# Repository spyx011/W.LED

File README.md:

# W LED Keychain

A keychain PCB with 13 blue LEDs in the shape of a W. It runs on a small LiPo battery and charges over USB-C.

## What's on it

- 13 blue 5mm LEDs in a W (front side)
- ATtiny1616 chip
- 2x 74HC595 and 2x ULN2003A to drive the LEDs
- LiPo battery on a JST connector, charged by USB-C
- Boost converter for 5V
- Slide switch and a push button
- My logo on the back

## Board

- 4 layers, 1.6mm, black solder mask
- Made in KiCad 10
- LEDs on the front, everything else on the back

- 

##3D model

## How the LEDs work

The ATtiny sends data to the two 74HC595 chips. They feed the ULN2003A chips, and those turn the LEDs on and off.

| ATtiny pin | Goes to |
|---|---|
| PA0 | UPDI header |
| PA1 | 595 data in |
| PA3 | 595 shift clock |
| PA4 | 595 latch |
| PB0 | 595 output enable (brightness) |
| PA6 | Push button |

## Programming

Turn the switch off, take the battery out, and connect a UPDI programmer to the 3 pin header (UPDI, 5V, GND).

## Files

- `hardware` - KiCad files
- `manufacturing` - Gerbers and BOM
- `docs` - pictures

Open `w.led.kicad_pro` in KiCad to see the design.

## Ordering

Pick 4 layers, 1.6mm, black solder mask. Use a LiPo with a protection board, because the charger chip doesn't protect the battery.

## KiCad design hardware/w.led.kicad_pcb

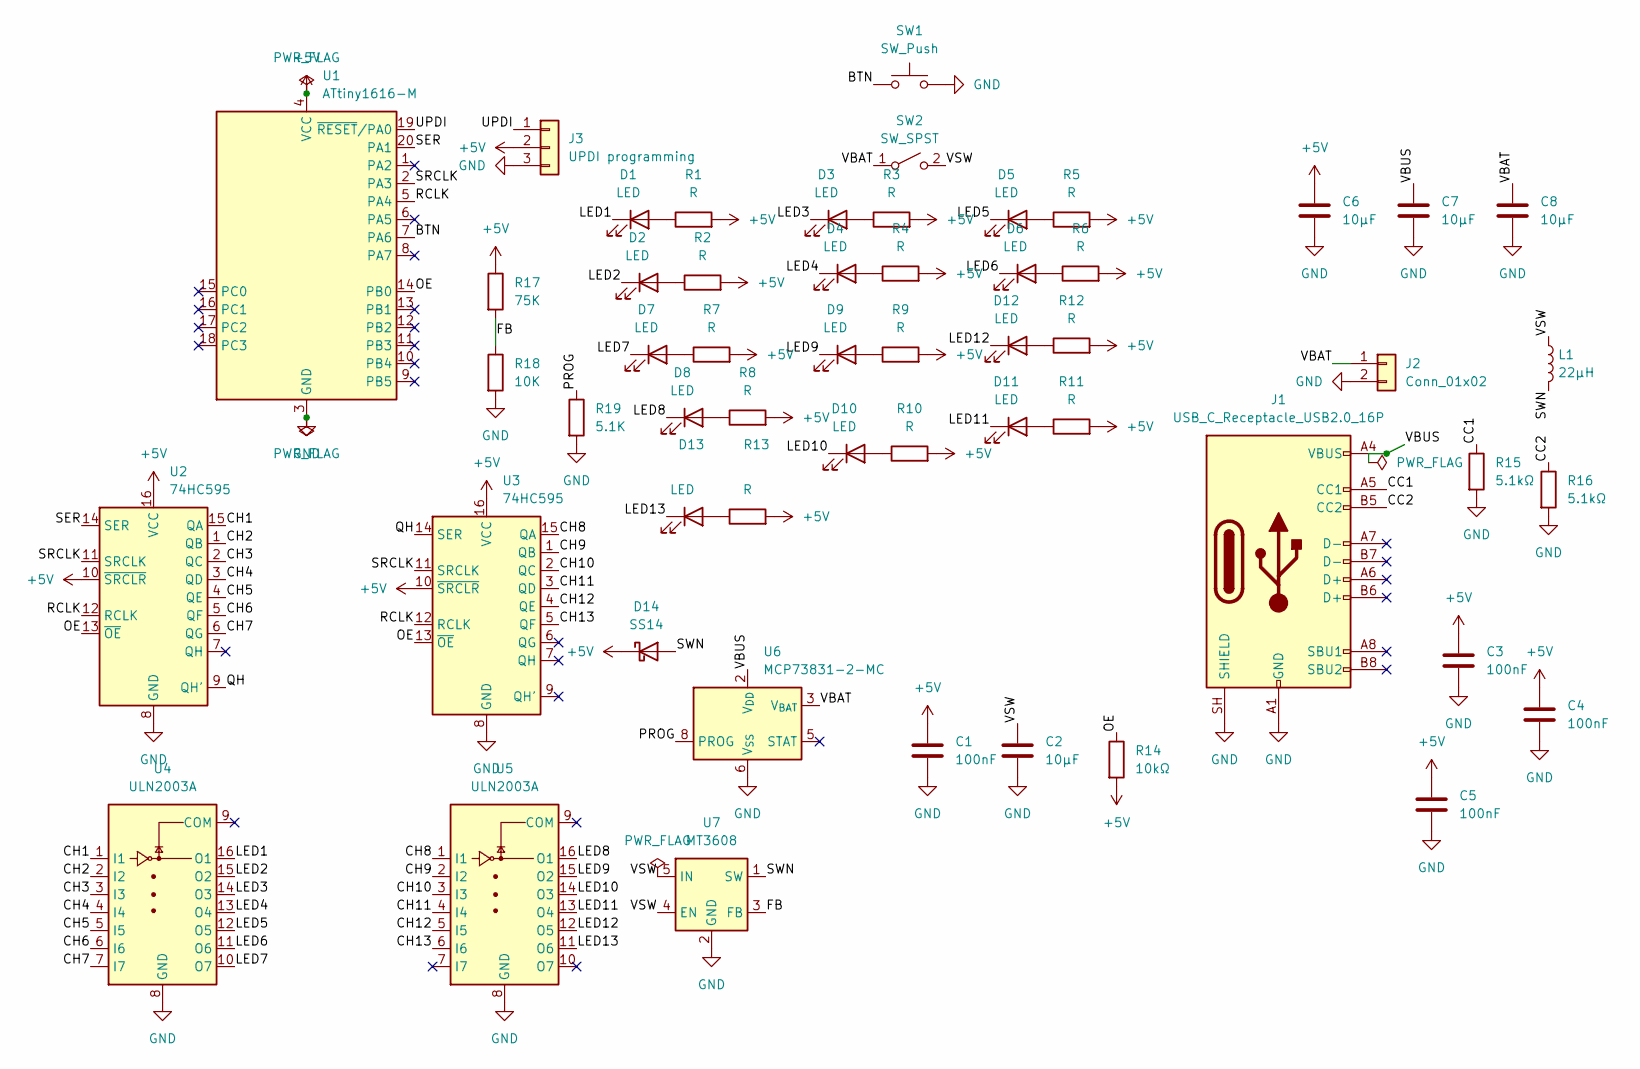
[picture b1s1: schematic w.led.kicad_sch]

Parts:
C1, C3, C4, C5: 100nF; C_0603_1608Metric
C2, C6, C7, C8: 10µF; C_0805_2012Metric
D1, D2, D3, D4, D5, D6, D7, D8, D9, D10, D11, D12, D13: LED; LED_D5.0mm
D14: SS14; D_SMA
J1: USB_C_Receptacle_USB2.0_16P; USB_C_Receptacle_GCT_USB4105-xx-A_16P_TopMnt_Horizontal
J2: Conn_01x02; JST_PH_B2B-PH-K_1x02_P2.00mm_Vertical
J3: UPDI programming; PinHeader_1x03_P2.54mm_Vertical
L1: 22µH; L_Taiyo-Yuden_NR-40xx
R1, R2, R3, R4, R5, R6, R7, R8, R9, R10, R11, R12, R13: R; R_0603_1608Metric
R14: 10kΩ; R_0603_1608Metric
R15, R16: 5.1kΩ; R_0603_1608Metric
R17: 75K; R_0603_1608Metric
R18: 10K; R_0603_1608Metric
R19: 5.1K; R_0603_1608Metric
SW1: SW_Push; SW_PUSH_6mm
SW2: SW_SPST; SW_SPDT_PCM12
U1: ATtiny1616-M; VQFN-20-1EP_3x3mm_P0.4mm_EP1.7x1.7mm
U2, U3: 74HC595; SOIC-16_3.9x9.9mm_P1.27mm
U4, U5: ULN2003A; SOIC-16_3.9x9.9mm_P1.27mm
U6: MCP73831-2-MC; DFN-8-1EP_3x2mm_P0.5mm_EP1.7x1.4mm
U7: MT3608; SOT-23-6

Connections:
+5V: C1.1, C3.1, C4.1, C5.1, C6.1, D14.1 (K), J3.2, R1.2, R2.2, R3.2, R4.2, R5.2, R6.2, R7.2, R8.2, R9.2, R10.2, R11.2, R12.2, R13.2, R14.2, R17.1, U1.4 (VCC), U2.10 (~SRCLR), U2.16 (VCC), U3.10 (~SRCLR), U3.16 (VCC)
/BTN: SW1.1, U1.7 (PA6)
/CC1: J1.A5 (CC1), R15.1
/CC2: J1.B5 (CC2), R16.1
/CH1: U2.15 (QA), U4.1 (I1)
/CH2: U2.1 (QB), U4.2 (I2)
/CH3: U2.2 (QC), U4.3 (I3)
/CH4: U2.3 (QD), U4.4 (I4)
/CH5: U2.4 (QE), U4.5 (I5)
/CH6: U2.5 (QF), U4.6 (I6)
/CH7: U2.6 (QG), U4.7 (I7)
/CH8: U3.15 (QA), U5.1 (I1)
/CH9: U3.1 (QB), U5.2 (I2)
/CH10: U3.2 (QC), U5.3 (I3)
/CH11: U3.3 (QD), U5.4 (I4)
/CH12: U3.4 (QE), U5.5 (I5)
/CH13: U3.5 (QF), U5.6 (I6)
/FB: R17.2, R18.1, U7.3 (FB)
/LED1: D1.1 (K), U4.16 (O1)
/LED2: D2.1 (K), U4.15 (O2)
/LED3: D3.1 (K), U4.14 (O3)
/LED4: D4.1 (K), U4.13 (O4)
/LED5: D5.1 (K), U4.12 (O5)
/LED6: D6.1 (K), U4.11 (O6)
/LED7: D7.1 (K), U4.10 (O7)
/LED8: D8.1 (K), U5.16 (O1)
/LED9: D9.1 (K), U5.15 (O2)
/LED10: D10.1 (K), U5.14 (O3)
/LED11: D11.1 (K), U5.13 (O4)
/LED12: D12.1 (K), U5.12 (O5)
/LED13: D13.1 (K), U5.11 (O6)
/OE: R14.1, U1.14 (PB0), U2.13 (~OE), U3.13 (~OE)
/PROG: R19.1, U6.8 (PROG)
/QH: U2.9 (QH'), U3.14 (SER)
/RCLK: U1.5 (PA4), U2.12 (RCLK), U3.12 (RCLK)
/SER: U1.20 (PA1), U2.14 (SER)
/SRCLK: U1.2 (PA3), U2.11 (SRCLK), U3.11 (SRCLK)
/SWN: D14.2 (A), L1.2, U7.1 (SW)
/UPDI: J3.1, U1.19 (~RESET/PA0)
/VBAT: C8.1, J2.1, SW2.1 (A), U6.3 (V_{BAT}), U6.4 (V_{BAT})
/VBUS: C7.1, J1.A4 (VBUS), J1.A9 (VBUS), J1.B4 (VBUS), J1.B9 (VBUS), U6.1 (V_{DD}), U6.2 (V_{DD})
/VSW: C2.1, L1.1, SW2.2 (B), U7.4 (EN), U7.5 (IN)
GND: C1.2, C2.2, C3.2, C4.2, C5.2, C6.2, C7.2, C8.2, J1.A1 (GND), J1.A12 (GND), J1.B1 (GND), J1.B12 (GND), J1.SH (SHIELD), J2.2, J3.3, R15.2, R16.2, R18.2, R19.2, SW1.2, U1.3 (GND), U1.21 (GND), U2.8 (GND), U3.8 (GND), U4.8 (GND), U5.8 (GND), U6.6 (V_{SS}), U7.2 (GND)
unnamed: D1.2 (A), R1.1
unnamed: D2.2 (A), R2.1
unnamed: D3.2 (A), R3.1
unnamed: D4.2 (A), R4.1
unnamed: D5.2 (A), R5.1
unnamed: D6.2 (A), R6.1
unnamed: D7.2 (A), R7.1
unnamed: D8.2 (A), R8.1
unnamed: D9.2 (A), R9.1
unnamed: D10.2 (A), R10.1
unnamed: D11.2 (A), R11.1
unnamed: D12.2 (A), R12.1
unnamed: D13.2 (A), R13.1

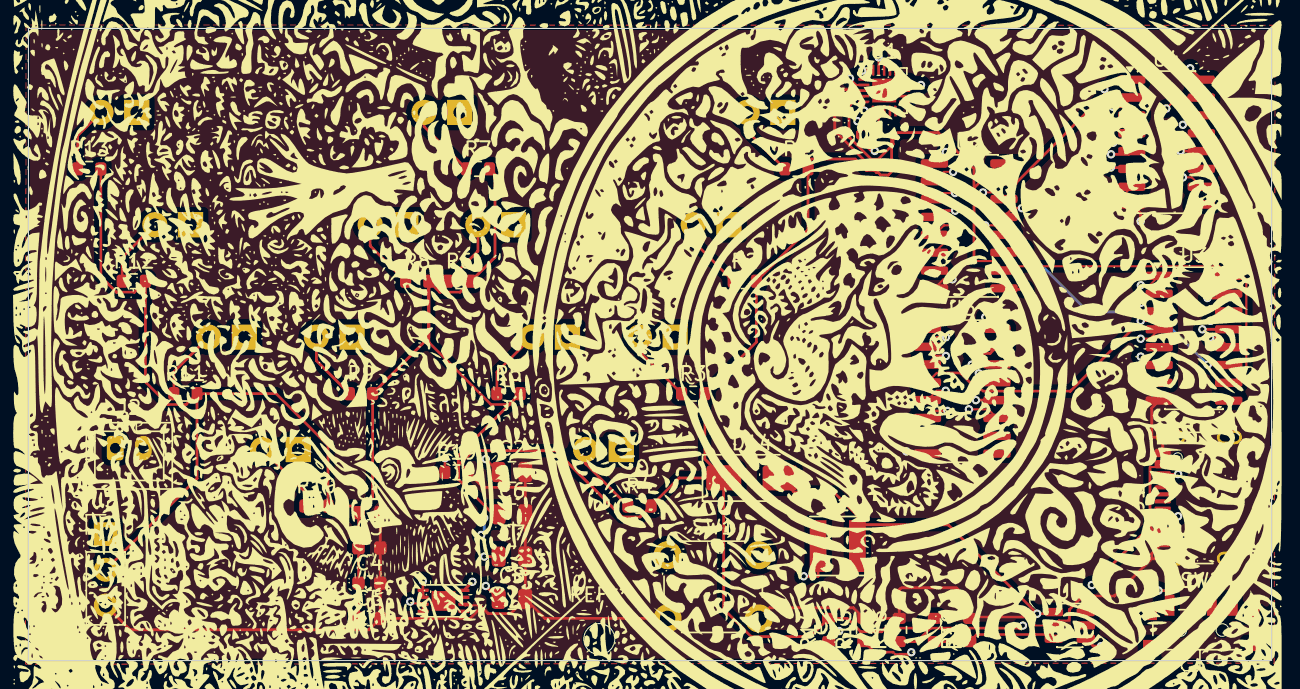
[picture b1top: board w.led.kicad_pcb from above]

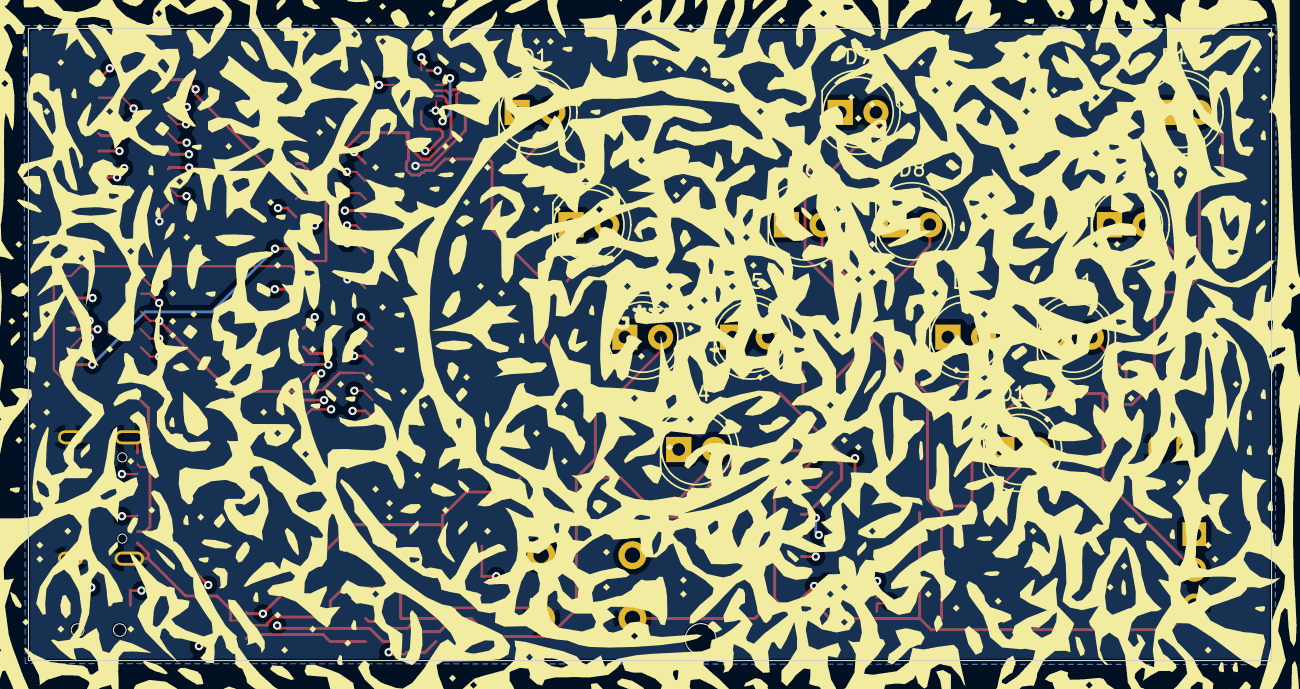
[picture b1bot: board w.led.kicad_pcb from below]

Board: 4 copper layers, 88.5 x 45.0 mm, 54 parts (13 on the bottom side), 56 nets.

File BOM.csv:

Designator,Qty,Value,Part,Footprint
U1,1,ATtiny1616,ATtiny1616-M,QFN-20-1EP_3x3mm_P0.4mm
"U2, U3",2,74HC595,74HC595,SOIC-16_3.9x9.9mm_P1.27mm
"U4, U5",2,ULN2003A,ULN2003A,SOIC-16_3.9x9.9mm_P1.27mm
U6,1,MCP73831-2,MCP73831-2-MC,DFN-8-1EP_3x2mm_P0.5mm
U7,1,MT3608,MT3608,SOT-23-6
D1-D13,13,Blue LED 5mm,LED,LED_D5.0mm
D14,1,SS14,SS14 Schottky diode,D_SMA
R1-R13,13,390R,Resistor,R_0603_1608Metric
"R14, R18",2,10k,Resistor,R_0603_1608Metric
"R15, R16, R19",3,5.1k,Resistor,R_0603_1608Metric
R17,1,75k,Resistor,R_0603_1608Metric
"C1, C3, C4, C5",4,100nF,Capacitor,C_0603_1608Metric
"C2, C6, C7, C8",4,10uF,Capacitor,C_0805_2012Metric
L1,1,22uH,Inductor 4x4mm,Check KiCad file
J1,1,USB-C,USB-C receptacle 16 pin,Check KiCad file
J2,1,JST-PH 2 pin,Battery connector,JST_PH_B2B-PH-K_1x02_P2.00mm_Vertical
J3,1,1x3 header,UPDI programming header,PinHeader_1x03_P2.54mm_Vertical
SW1,1,6x6 button,Push button,SW_PUSH_6mm
SW2,1,Slide switch,Slide switch,Check KiCad file
BT (not on board),1,3.7V LiPo 300-500mAh,LiPo with protection board and JST-PH plug,-
